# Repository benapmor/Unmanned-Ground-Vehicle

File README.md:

# Unmanned-Ground-Vehicle

This is the Repository for the Unmanned Ground Vehicle Project.

**Please Note that this is an ongoing project**

As of March 11th 2021 the following has been completed:

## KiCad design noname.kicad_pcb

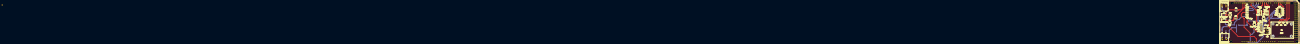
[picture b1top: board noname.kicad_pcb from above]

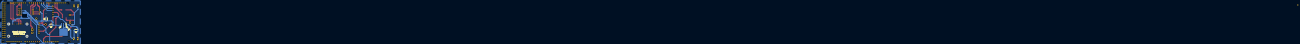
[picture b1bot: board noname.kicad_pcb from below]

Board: 2 copper layers, 22 parts (4 on the bottom side), 21 nets.

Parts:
BZ1: Buzzer; JWT_A3963_1x02_P3.96mm_Vertical
C1, C2, C3: 100n; C_2010_5025Metric_Pad1.52x2.65mm_HandSolder
D2: TX Indicator; LED_2010_5025Metric
D3: RX Indicator; LED_2010_5025Metric
M1: Steering Servo; PinHeader_1x03_P2.54mm_Vertical
M2: Turret_Servo; PinHeader_1x03_P2.54mm_Vertical
MicroBattery1: 9.6V; TerminalBlock_Altech_AK300-2_P5.00mm
MotorBattery1: 12V; TerminalBlock_Altech_AK300-2_P5.00mm
R2, R3: 330; R_2010_5025Metric_Pad1.52x2.65mm_HandSolder
TP2: 5v Test; TestPoint_Keystone_5010-5014_Multipurpose
TP3: Relay signal test; TestPoint_Keystone_5010-5014_Multipurpose
TP4: WIFI TX TEST; TestPoint_Keystone_5010-5014_Multipurpose
TP5: WIFI RX test; TestPoint_Keystone_5010-5014_Multipurpose
U1: L7805; TO-263-3_TabPin2
U2: Mega; Ardunio_mega
U3: H-bridge; PinHeader_1x06_P2.54mm_Vertical
U4: IMU
U5: Relay; PinHeader_1x06_P2.54mm_Vertical
U6: wifi; PinSocket_2x04_P2.54mm_Vertical

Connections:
3.3V: U2.74, U4.1, U6.1, U6.3, U6.5
5V: U2.73, U3.4, U5.5
9.6V: MicroBattery1.1, U2.70
12V: C1.1, MotorBattery1.1, U1.1, U3.6, U5.2
GND: BZ1.2, C1.2, C2.2, C3.2, D2.1, D3.1, M1.3, M2.3, MicroBattery1.2, MotorBattery1.2, U1.2, U2.71, U2.72, U3.5, U4.2, U5.4, U6.8
IN0_A: U2.7, U3.2
IN0_B: U2.6, U3.3
unnamed: BZ1.1, U2.2
unnamed: C2.1, C3.1, M1.2, M2.2, TP2.1, U1.3
unnamed: D2.2, R2.1, TP4.1
unnamed: D3.2, R3.1, TP5.1
unnamed: R2.2, U2.13
unnamed: R3.2, U2.12
unnamed: U2.16, U6.7
unnamed: U2.17, U6.2
PWM_A: U2.8, U3.1
S1: M1.1, U2.4
S2: M2.1, U2.3
SCL: U2.21, U4.4
SDA: U2.20, U4.3
Sig: TP3.1, U2.9, U5.6

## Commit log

2021-03-12 Add Arduino code
2021-03-12 Added Graphical User Interface Code
2021-03-12 Added Software Architecture Diagram
2021-05-14 Create PCB files
2021-05-14 PCB layout file
2021-09-26 Add files via upload
    ADDED video of vehicle
